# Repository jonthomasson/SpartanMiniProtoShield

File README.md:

# SpartanMiniProtoShield
A proto/perfboard shield for the Spartan Mini FPGA development board

![enter image description here](https://lh3.googleusercontent.com/2wbPRz-nE1Fc0jCA2f07u5Me2V3H0UNUPrMFlLz3Twl0Yg7VeR5VOPqTKE0uDzywc4r05hFo4VHKxLDwUGt4AwSnZAaZkKsiXd9adMtz0fSHwO1DeRkM1_eBWd0WBOogVniMLl2L2cgKlpiEYo8FboDsb1nUN32IObfpBDq2vlQJhA5I2vb10pKMYY1vehKfrYLQuY_Zlh-YrsaNNhH5CbYEC6idkpA1AZDaOXOrPSAnS7jUr5EUhx1EIJVqBJlHOdIWO9OVjuv_jyUrRz5-Z4mwdfUDqM1IafEKwZUJDONwqSEysahrEuyYSCqwEHpiWuu1_euHWjV-lfo3SKZtZdNi4HIS1XkY0xOoQtB6_pXjHYLyHN9QsgzdODhzv6rUVm3ibE5WrTlHqlcNlxiArEMgLfdJpx5dNdbc_YCcuPN5Y6AVRe_zen7nu0x08xv6PcMZG4pDprgElbqOCxHCT7nAqFGeomliq8rcjdViluc7DenpiapIowLsyH_k2eMeFFRcEHxFmpeD0bXLOA9wijhxU-p-tScMewFEHZ686iMinjoxK3GBW3e_kd_2ow89t5gs3pH5pFPJa1QrME-cBf1KRHg0vg2SkGAANUXq=w1688-h949-no)

![enter image description here](https://lh3.googleusercontent.com/eeefYKwcRdxxkHmTPi6D5s8xJRYnAHaJXIY_S74f9kfCOiNwfqJWBo3RRuFCKG3pkpjW_MOPYPIFANHKSdgG7zIbD3iJhS0fh_G7nJ1YLpcCfIFpnByOlFWNmZsTXUf8obblsHgcW4ngKCjrV8hUlIvO5yguO3xboJWBDKGeqdaRV-OVYuQEbc93ienMqZIW4HLuNXQxlkSTl3B90KRuGfjQdlPjrq158nac027gjcpQUIr9y2HV9N5HFQmAzGrY37y7gFtuCXeSVXeVe4iLq2mg7VONuE-e2-9HwmFmQ5tz3fMsk-PIWOjzBabLXf_KzeoYV0-ZvPk_YA8MG1haDm_4JOUpVfa9gMx4jAFAGEtJF8sS0VJyimWUc0sugu1ytpZQZI5Dn0qjh6jnlRThrepD3b2oDW14G1AMkfNVC_yFMFf_rqiFoxQ7p_3XLB-QHSVD7XNn9fPk1JSXIleet39pnrnbAjOJiSwwxHf44C0gVR6tvATM0qlyaUNI3DtDN0vCbXIgDY8v2REErIxis63WkERT9Mtce4OJljkHyCwXzpxGe3D0dIxquZcOAwdErh5NEx2gPwp3kfWFIUshTdS3cWxjYE5Mm0evnET3=w1688-h949-k-no)

![enter image description here](https://lh3.googleusercontent.com/nBNiuSj_IdoI4wbylTjWe8ktIL3MoXxaDYgPPBEDJ3AYpXOrVAGqRX6b4bckdKY1lS7-5gFGHc0N_uYtWvcO5nT1lnXsf_jSYu6Rf45XtT1m77WLzpYW5jfe6YW-9u6VfxUyb1-iAz6D6x44Jhl5GO3lYm9ROuz088B5WYXPwpRf8uNRb4YMgErAdq8aCB4ZcMbgKeoqjoD_xJIPtC57Q_sxvkAMqUWkcYqR0o7GZyN8slMQ2wgeOCywj55JylHCUN5zGhMWPkXzdw30tsIuUQZgnysnF6hadnzpeLvQDwcXxvUWXgW9jc0fc1S-Q2P5o7PbYBhQZ6iVM20pUVJmGk1obGl_eJbKdMSYeeper_sLhDbzaF3_E8iQZxuC3lGxgr4cX8u5H1Yd_VbKCrtm8W_tqCRUXNmM_p-Mv0Oent62g6tO99K1UKfuvMQDkNixkdxv3ER3fIpx0VEMYooHULkDcP6znRD9SVVJ5qjWEweBFccARtlKVLSdgA-VaXuxWvmLHlA4PJV2HwmJ1UFDQz4qymGAJbXNoZeialkTuvqaWMjBEpgBB7v4uJaCV1708uLZkmL9yeNVVAvU4f0Ae_x-9WOKpI6n_ya10LSSg1dZSFa5U7Dz3y7hzu8MeQl2Vpoly-01VUTkoVSOEBXCNMawG6nJva0YHw=w1416-h796-no)

As used in the [Spartan Mini NES](https://github.com/jonthomasson/Spartan-Mini-NES) project.

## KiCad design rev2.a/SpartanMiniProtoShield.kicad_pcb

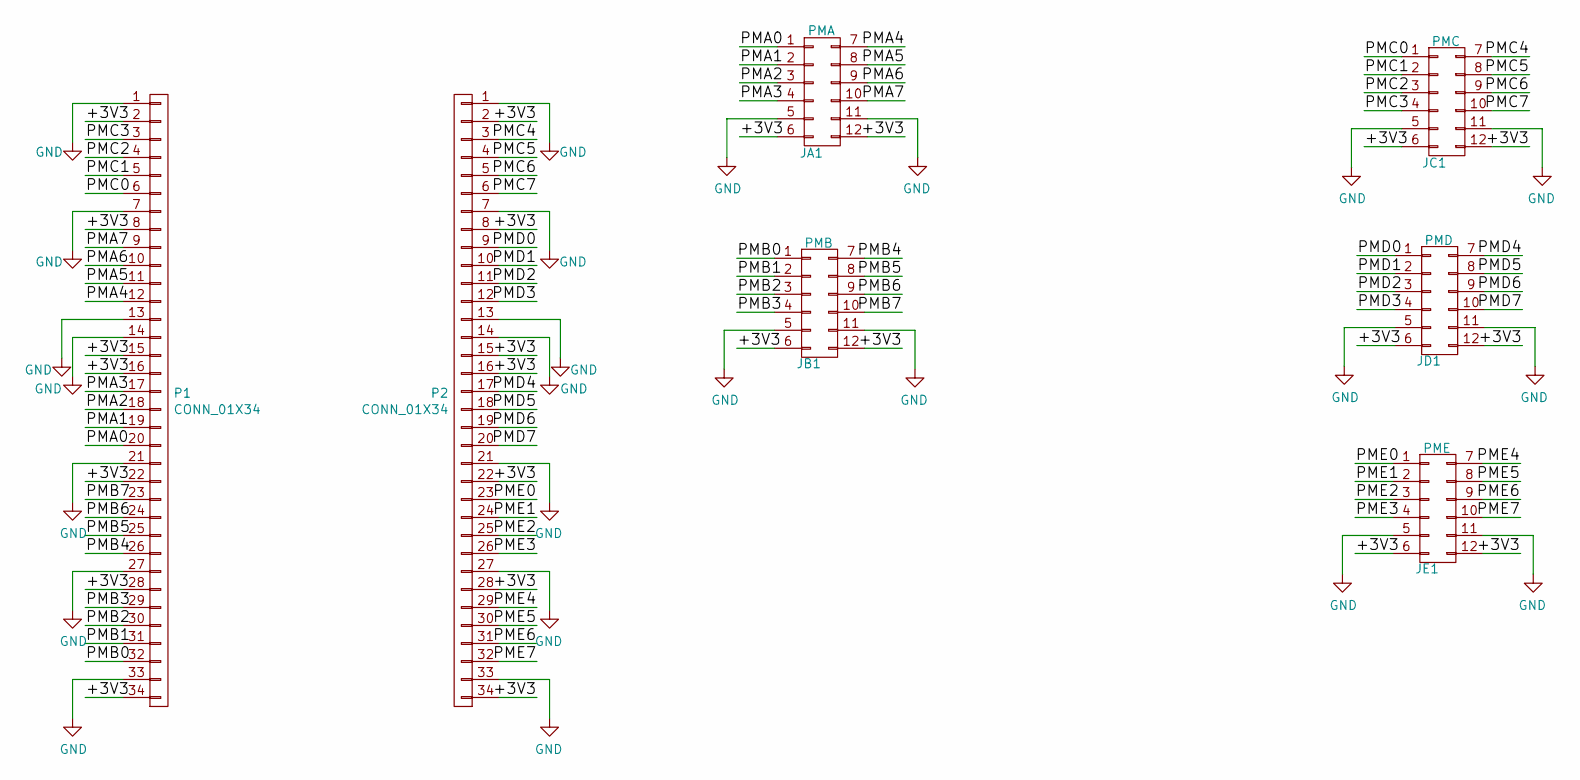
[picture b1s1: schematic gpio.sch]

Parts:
JA1: PMA; Pin_Header_Straight_2x06
JB1: PMB; Pin_Header_Straight_2x06
JC1: PMC; Pin_Header_Straight_2x06
JD1: PMD; Pin_Header_Straight_2x06
JE1: PME; Pin_Header_Straight_2x06
P1, P2: CONN_01X34; Socket_Strip_Straight_1x34

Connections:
/gpio/+3V3: JA1.6, JA1.12, JB1.6, JB1.12, JC1.6, JC1.12, JD1.6, JD1.12, JE1.6, JE1.12, P1.2, P1.8, P1.15, P1.16, P1.22, P1.28, P1.34, P2.2, P2.8, P2.15, P2.16, P2.22, P2.28, P2.34
/gpio/PMA0: JA1.1, P1.20
/gpio/PMA1: JA1.2, P1.19
/gpio/PMA2: JA1.3, P1.18
/gpio/PMA3: JA1.4, P1.17
/gpio/PMA4: JA1.7, P1.12
/gpio/PMA5: JA1.8, P1.11
/gpio/PMA6: JA1.9, P1.10
/gpio/PMA7: JA1.10, P1.9
/gpio/PMB0: JB1.1, P1.32
/gpio/PMB1: JB1.2, P1.31
/gpio/PMB2: JB1.3, P1.30
/gpio/PMB3: JB1.4, P1.29
/gpio/PMB4: JB1.7, P1.26
/gpio/PMB5: JB1.8, P1.25
/gpio/PMB6: JB1.9, P1.24
/gpio/PMB7: JB1.10, P1.23
/gpio/PMC0: JC1.1, P1.6
/gpio/PMC1: JC1.2, P1.5
/gpio/PMC2: JC1.3, P1.4
/gpio/PMC3: JC1.4, P1.3
/gpio/PMC4: JC1.7, P2.3
/gpio/PMC5: JC1.8, P2.4
/gpio/PMC6: JC1.9, P2.5
/gpio/PMC7: JC1.10, P2.6
/gpio/PMD0: JD1.1, P2.9
/gpio/PMD1: JD1.2, P2.10
/gpio/PMD2: JD1.3, P2.11
/gpio/PMD3: JD1.4, P2.12
/gpio/PMD4: JD1.7, P2.17
/gpio/PMD5: JD1.8, P2.18
/gpio/PMD6: JD1.9, P2.19
/gpio/PMD7: JD1.10, P2.20
/gpio/PME0: JE1.1, P2.23
/gpio/PME1: JE1.2, P2.24
/gpio/PME2: JE1.3, P2.25
/gpio/PME3: JE1.4, P2.26
/gpio/PME4: JE1.7, P2.29
/gpio/PME5: JE1.8, P2.30
/gpio/PME6: JE1.9, P2.31
/gpio/PME7: JE1.10, P2.32
GND: JA1.5, JA1.11, JB1.5, JB1.11, JC1.5, JC1.11, JD1.5, JD1.11, JE1.5, JE1.11, P1.1, P1.7, P1.13, P1.14, P1.21, P1.27, P1.33, P2.1, P2.7, P2.13, P2.14, P2.21, P2.27, P2.33

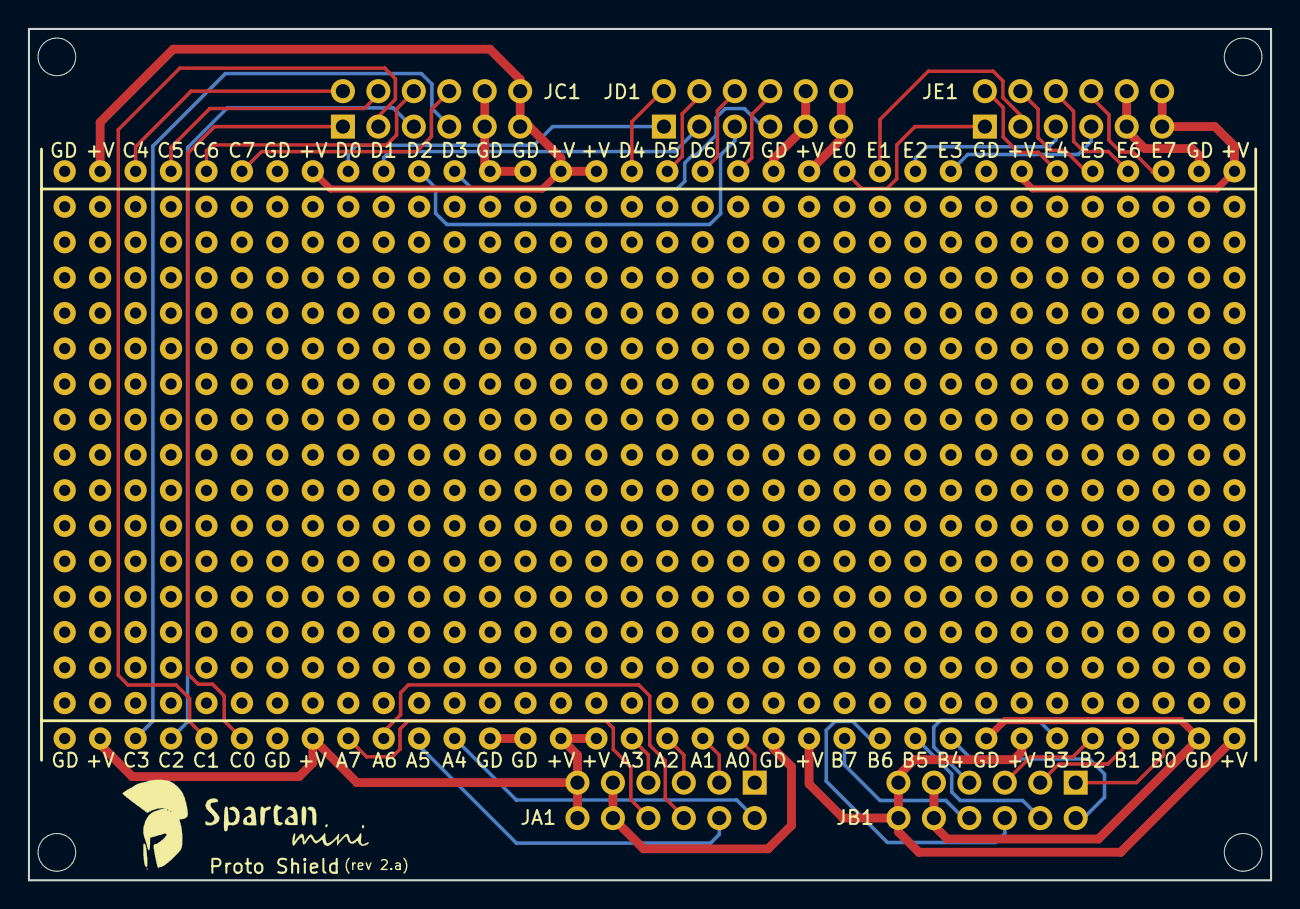
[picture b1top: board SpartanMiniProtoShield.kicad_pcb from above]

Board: 2 copper layers, 89.0 x 61.0 mm, 7 parts (0 on the bottom side), 42 nets.

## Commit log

2017-05-26 :boom::camel: Added .gitattributes & .gitignore files
2017-08-14 added rev 2.a changes
2017-09-24 finished routing and added gerber
